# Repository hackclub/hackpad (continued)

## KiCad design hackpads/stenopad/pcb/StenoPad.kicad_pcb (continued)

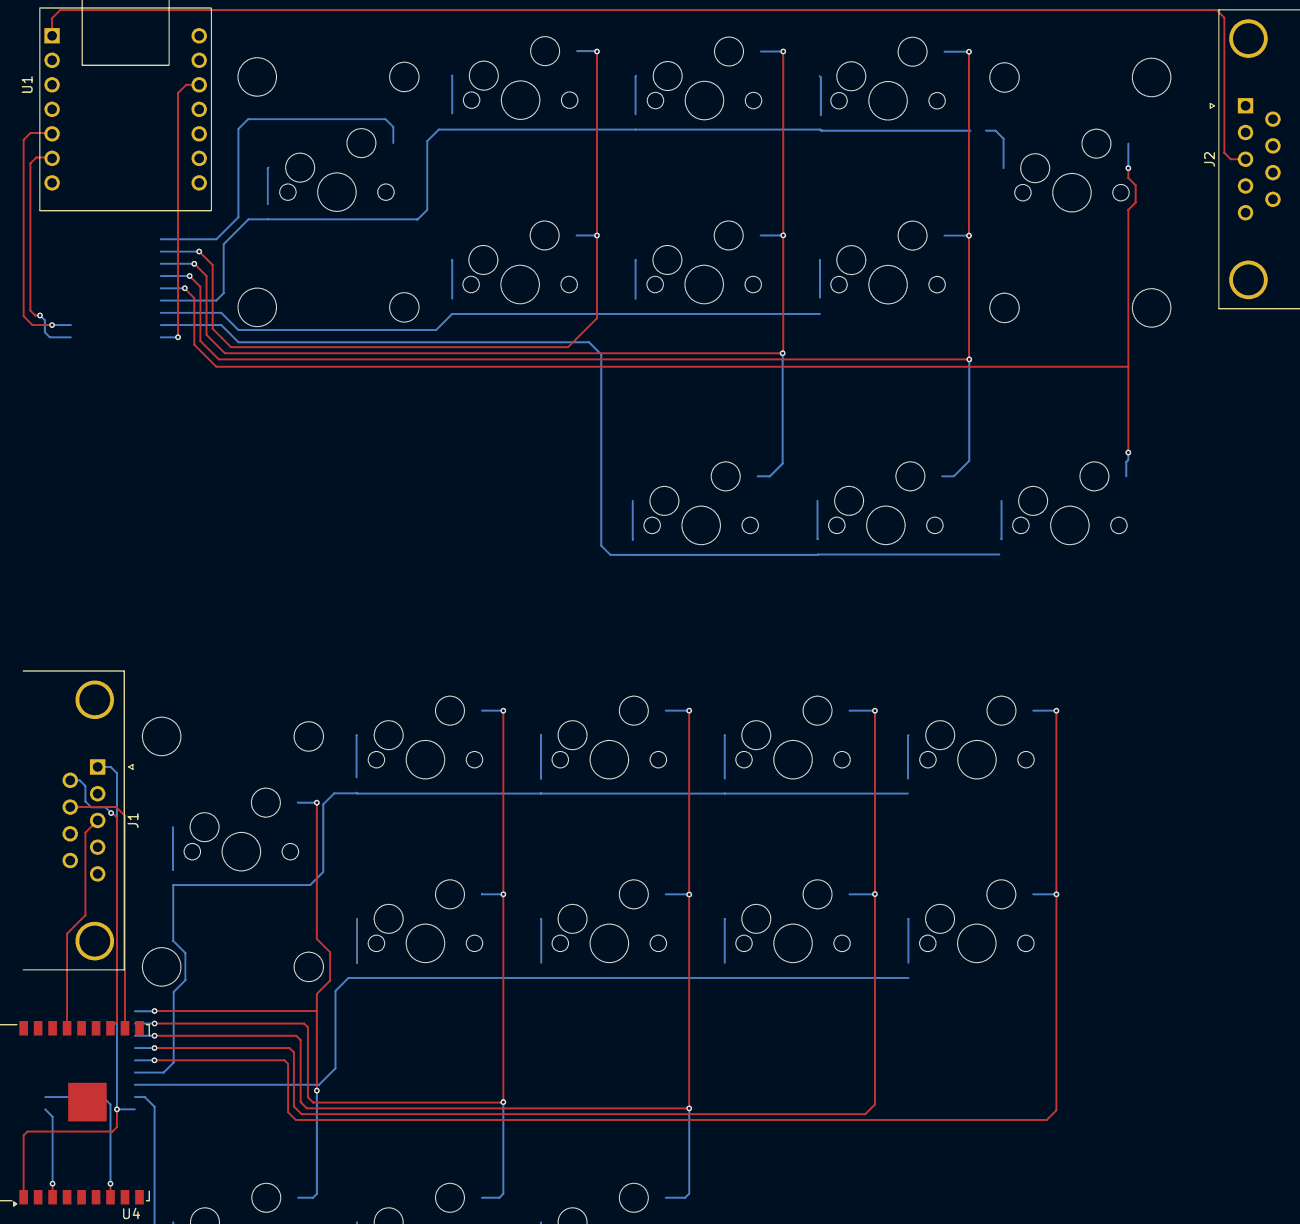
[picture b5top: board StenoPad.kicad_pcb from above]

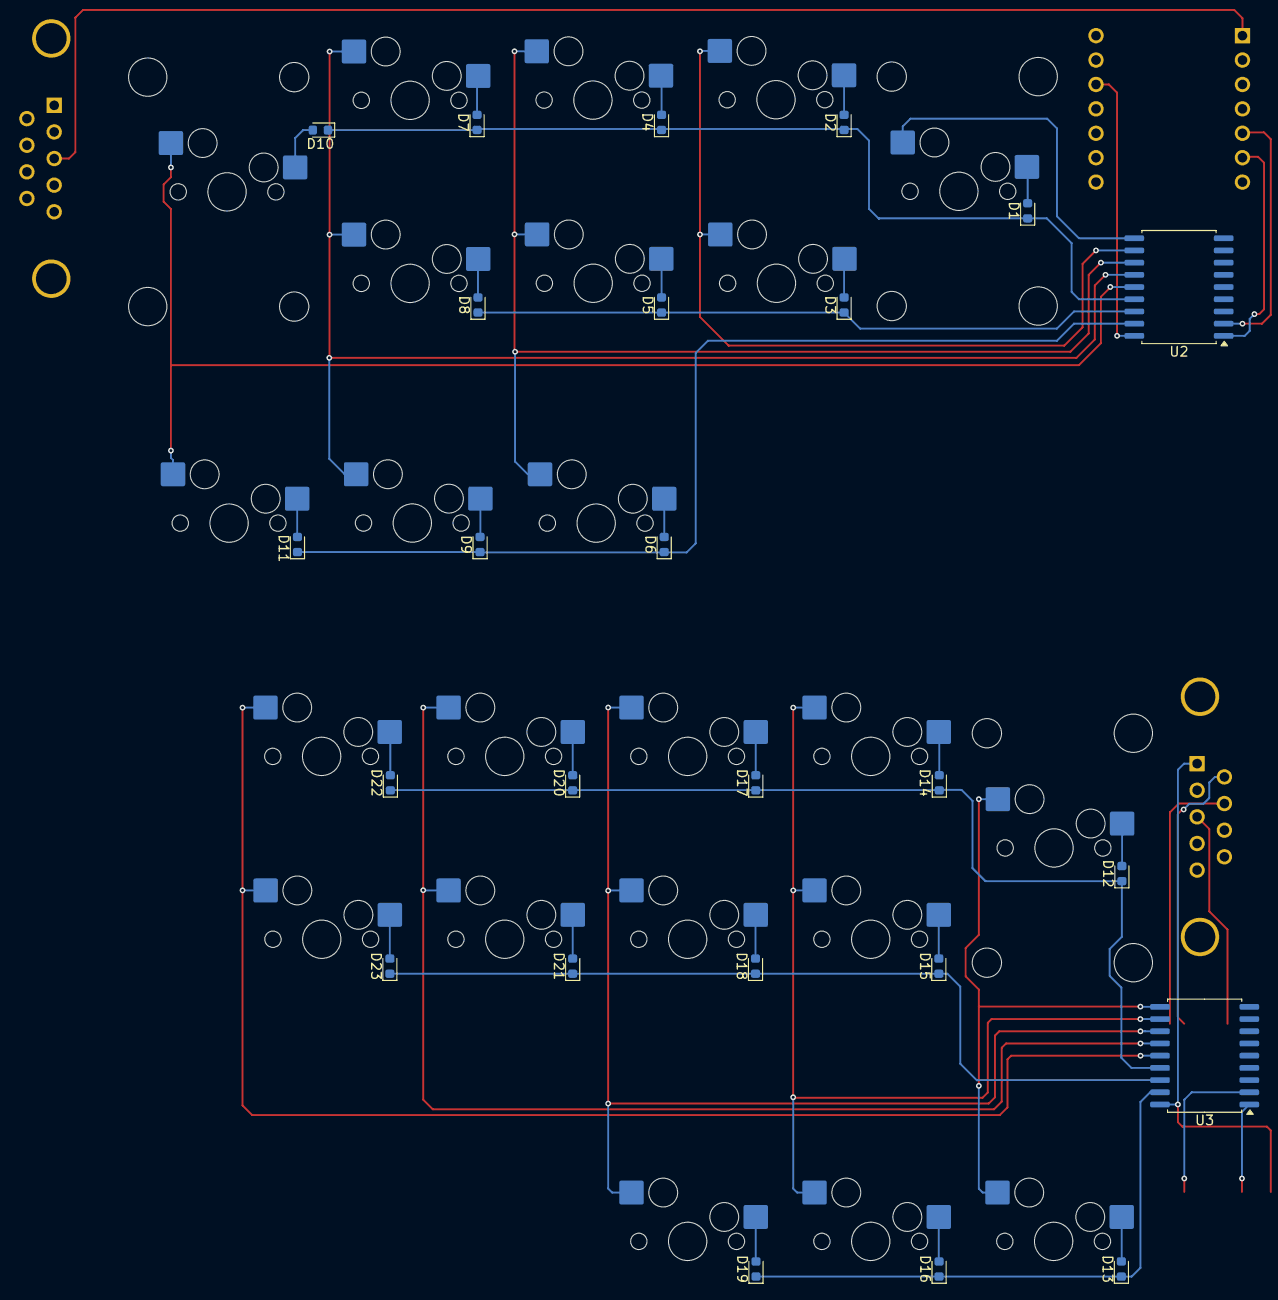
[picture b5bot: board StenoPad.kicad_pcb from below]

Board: 2 copper layers, 52 parts (48 on the bottom side), 54 nets.

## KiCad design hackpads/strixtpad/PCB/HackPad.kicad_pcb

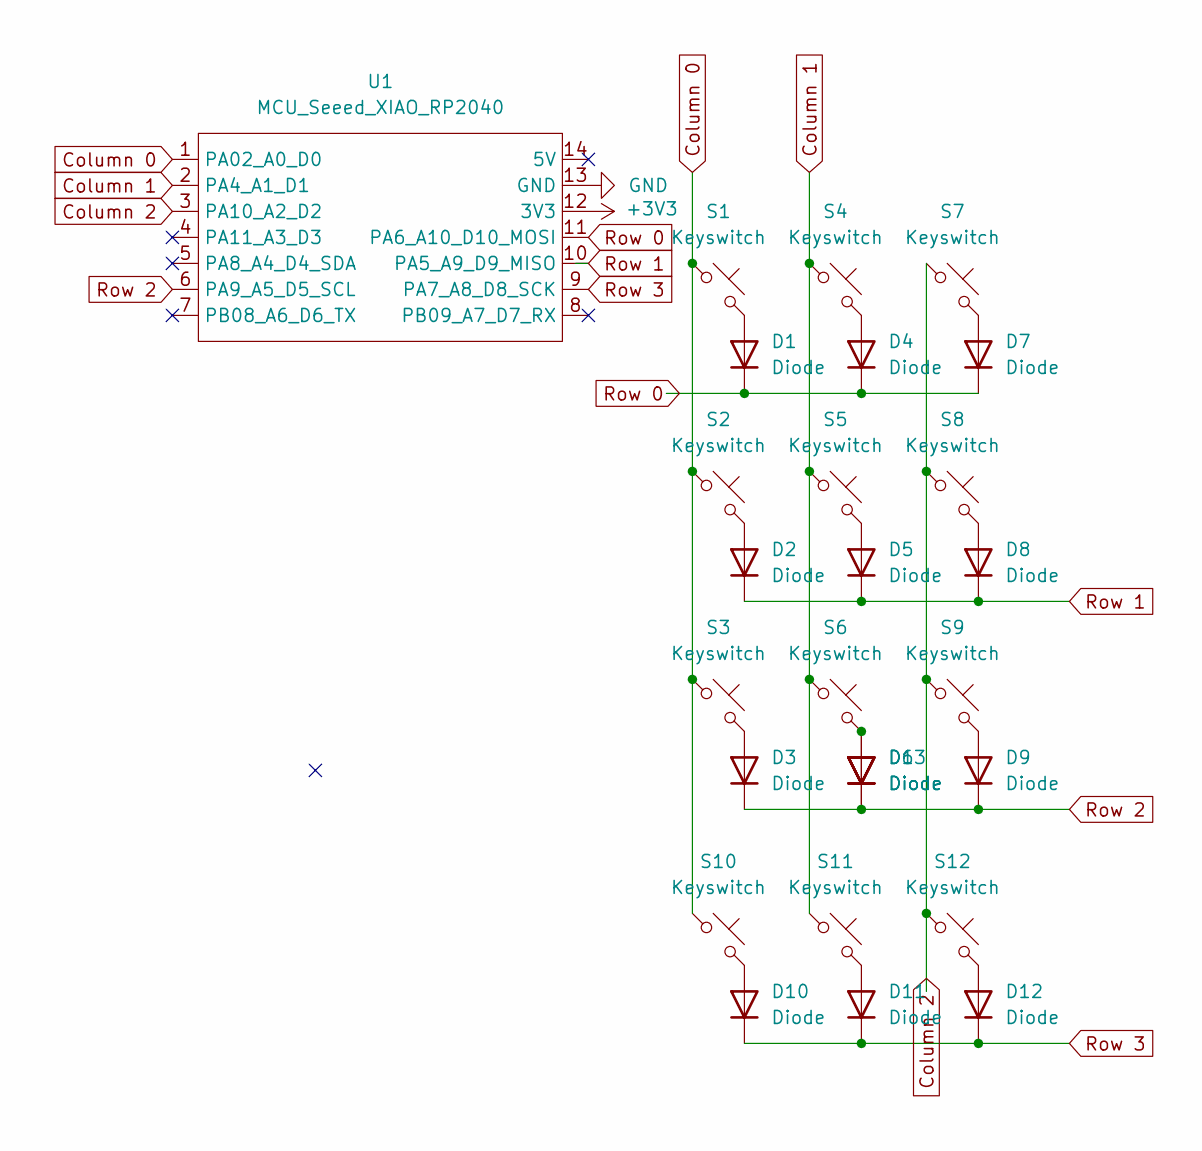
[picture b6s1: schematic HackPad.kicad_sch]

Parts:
D1, D2, D3, D4, D5, D6, D7, D8, D9, D10, D11, D12, D13: Diode; Diode_DO-35
S1, S2, S3, S4, S5, S6, S7, S8, S9, S10, S11, S12: Keyswitch; MX_PCB_1.00u
U1: MCU_Seeed_XIAO_RP2040; Seeed_XIAO_RP2040

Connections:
+3V3: U1.12 (3V3)
Column 0: S1.1, S2.1, S3.1, S10.1, U1.1 (PA02_A0_D0)
Column 1: S4.1, S5.1, S6.1, S11.1, U1.2 (PA4_A1_D1)
Column 2: S7.1, S8.1, S9.1, S12.1, U1.3 (PA10_A2_D2)
GND: U1.13 (GND)
unnamed: D1.2 (A), S1.2
unnamed: D2.2 (A), S2.2
unnamed: D3.2 (A), S3.2
unnamed: D4.2 (A), S4.2
unnamed: D5.2 (A), S5.2
unnamed: D6.2 (A), D13.2 (A), S6.2
unnamed: D7.2 (A), S7.2
unnamed: D8.2 (A), S8.2
unnamed: D9.2 (A), S9.2
unnamed: D10.2 (A), S10.2
unnamed: D11.2 (A), S11.2
unnamed: D12.2 (A), S12.2
Row 0: D1.1 (K), D4.1 (K), D7.1 (K), U1.11 (PA6_A10_D10_MOSI)
Row 1: D2.1 (K), D5.1 (K), D8.1 (K), U1.10 (PA5_A9_D9_MISO)
Row 2: D3.1 (K), D6.1 (K), D9.1 (K), D13.1 (K), U1.6 (PA9_A5_D5_SCL)
Row 3: D10.1 (K), D11.1 (K), D12.1 (K), U1.9 (PA7_A8_D8_SCK)

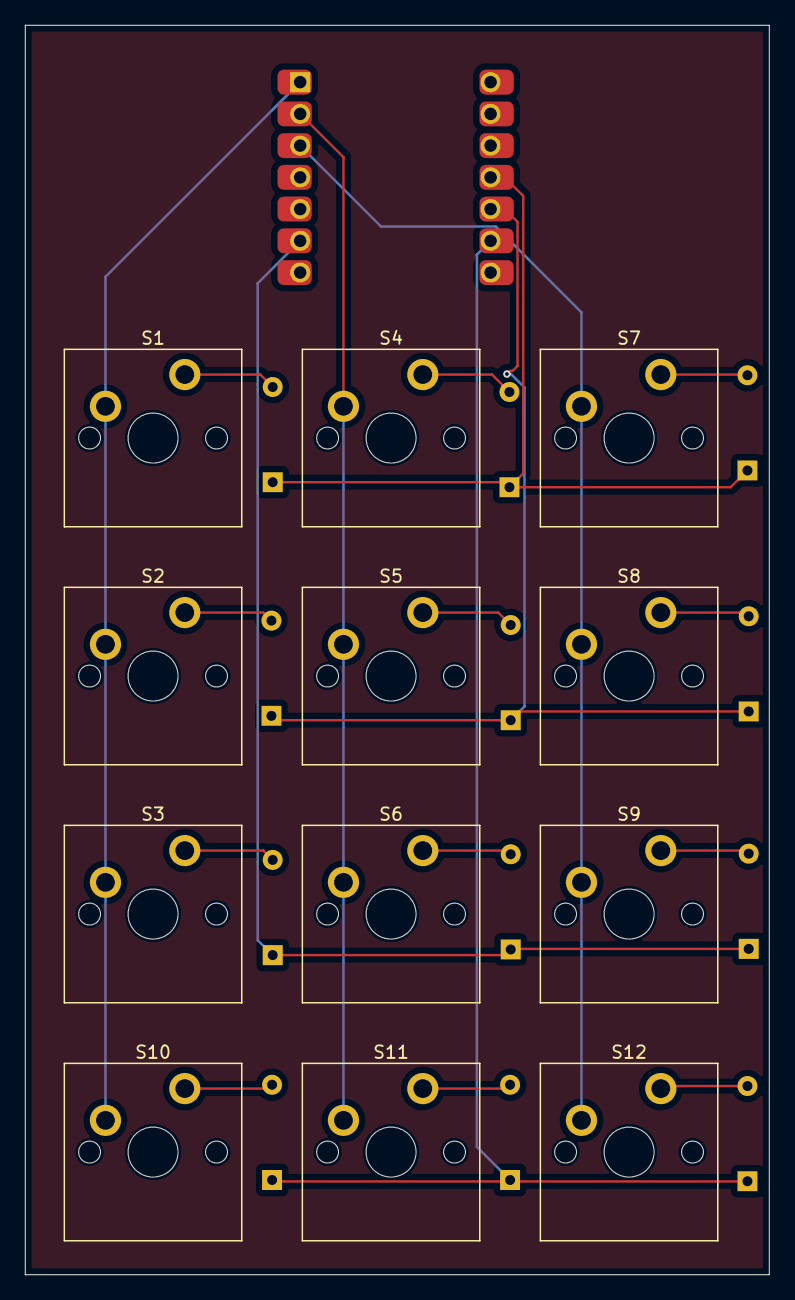
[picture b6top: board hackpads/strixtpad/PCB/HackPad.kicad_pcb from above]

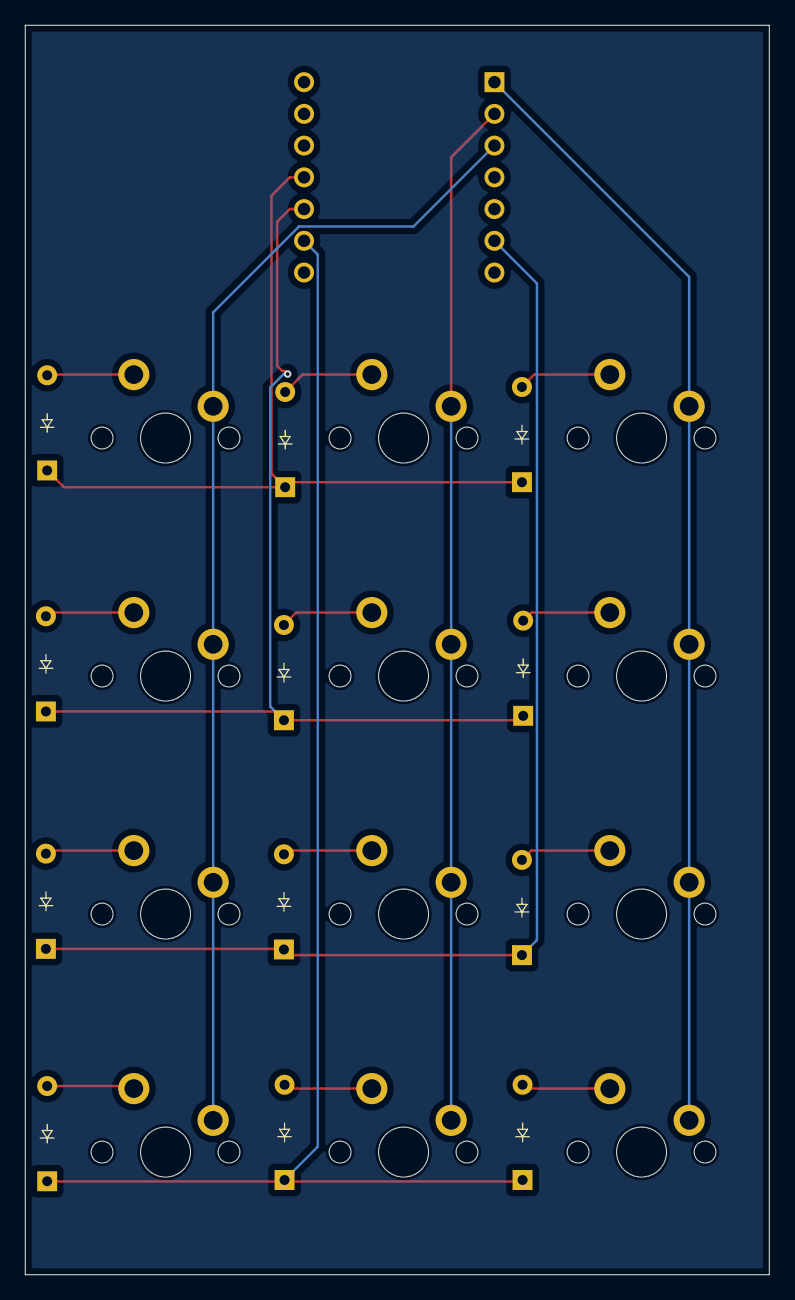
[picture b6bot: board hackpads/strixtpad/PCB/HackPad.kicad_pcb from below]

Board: 2 copper layers, 59.5 x 100.0 mm, 25 parts (12 on the bottom side), 19 nets.

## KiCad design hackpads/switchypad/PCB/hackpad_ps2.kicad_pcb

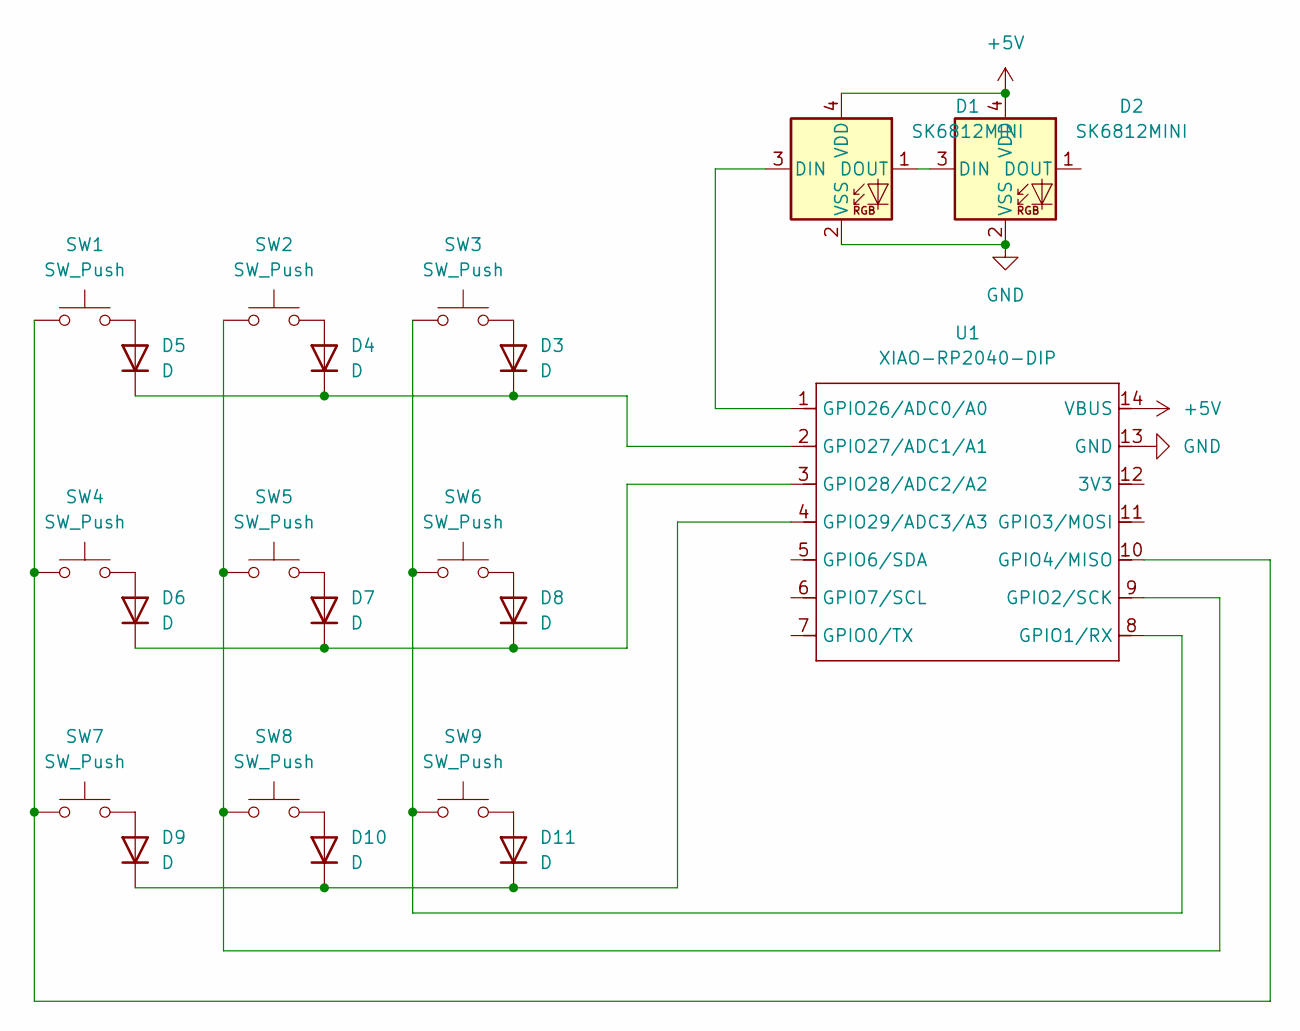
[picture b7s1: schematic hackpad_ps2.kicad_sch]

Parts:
D1, D2: SK6812MINI; LED_SK6812MINI_PLCC4_3.5x3.5mm_P1.75mm
D3, D4, D5, D6, D7, D8, D9, D10, D11: D; D_DO-35_SOD27_P7.62mm_Horizontal
SW1, SW2, SW3, SW4, SW5, SW6, SW7, SW8, SW9: SW_Push; SW_Cherry_MX_1.00u_PCB
U1: XIAO-RP2040-DIP

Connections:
+5V: D1.4 (VDD), D2.4 (VDD), U1.14 (VBUS)
GND: D1.2 (VSS), D2.2 (VSS), U1.13 (GND)
unnamed: D1.3 (DIN), U1.1 (GPIO26/ADC0/A0)
unnamed: D1.1 (DOUT), D2.3 (DIN)
unnamed: D3.2 (A), SW3.2
unnamed: D3.1 (K), D4.1 (K), D5.1 (K), U1.2 (GPIO27/ADC1/A1)
unnamed: D4.2 (A), SW2.2
unnamed: D5.2 (A), SW1.2
unnamed: D6.2 (A), SW4.2
unnamed: D6.1 (K), D7.1 (K), D8.1 (K), U1.3 (GPIO28/ADC2/A2)
unnamed: D7.2 (A), SW5.2
unnamed: D8.2 (A), SW6.2
unnamed: D9.2 (A), SW7.2
unnamed: D10.2 (A), SW8.2
unnamed: D9.1 (K), D10.1 (K), D11.1 (K), U1.4 (GPIO29/ADC3/A3)
unnamed: D11.2 (A), SW9.2
unnamed: SW3.1, SW6.1, SW9.1, U1.8 (GPIO1/RX)
unnamed: SW2.1, SW5.1, SW8.1, U1.9 (GPIO2/SCK)
unnamed: SW1.1, SW4.1, SW7.1, U1.10 (GPIO4/MISO)

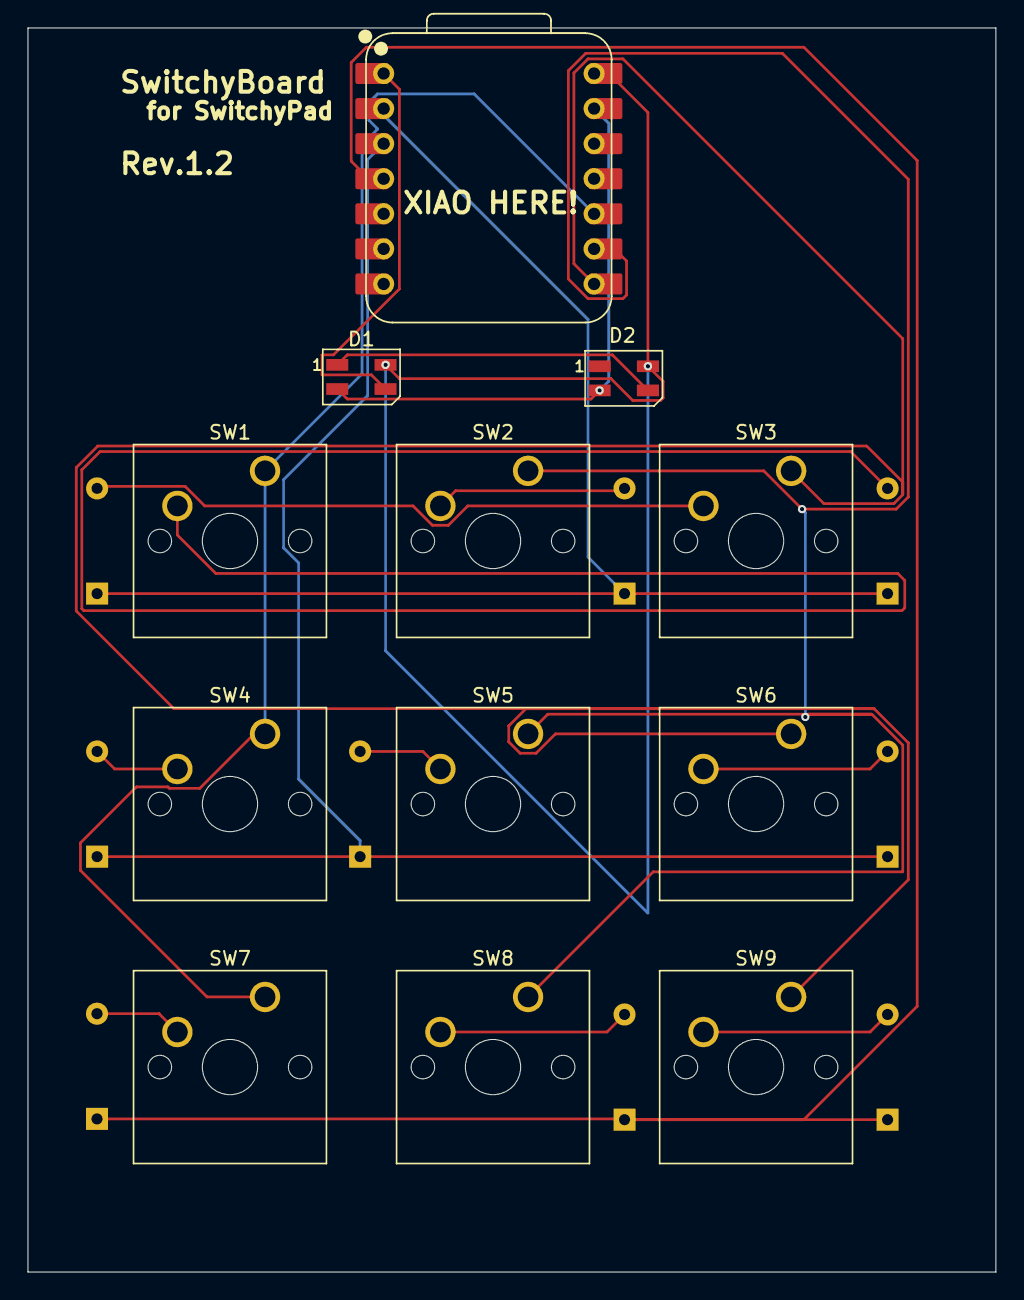
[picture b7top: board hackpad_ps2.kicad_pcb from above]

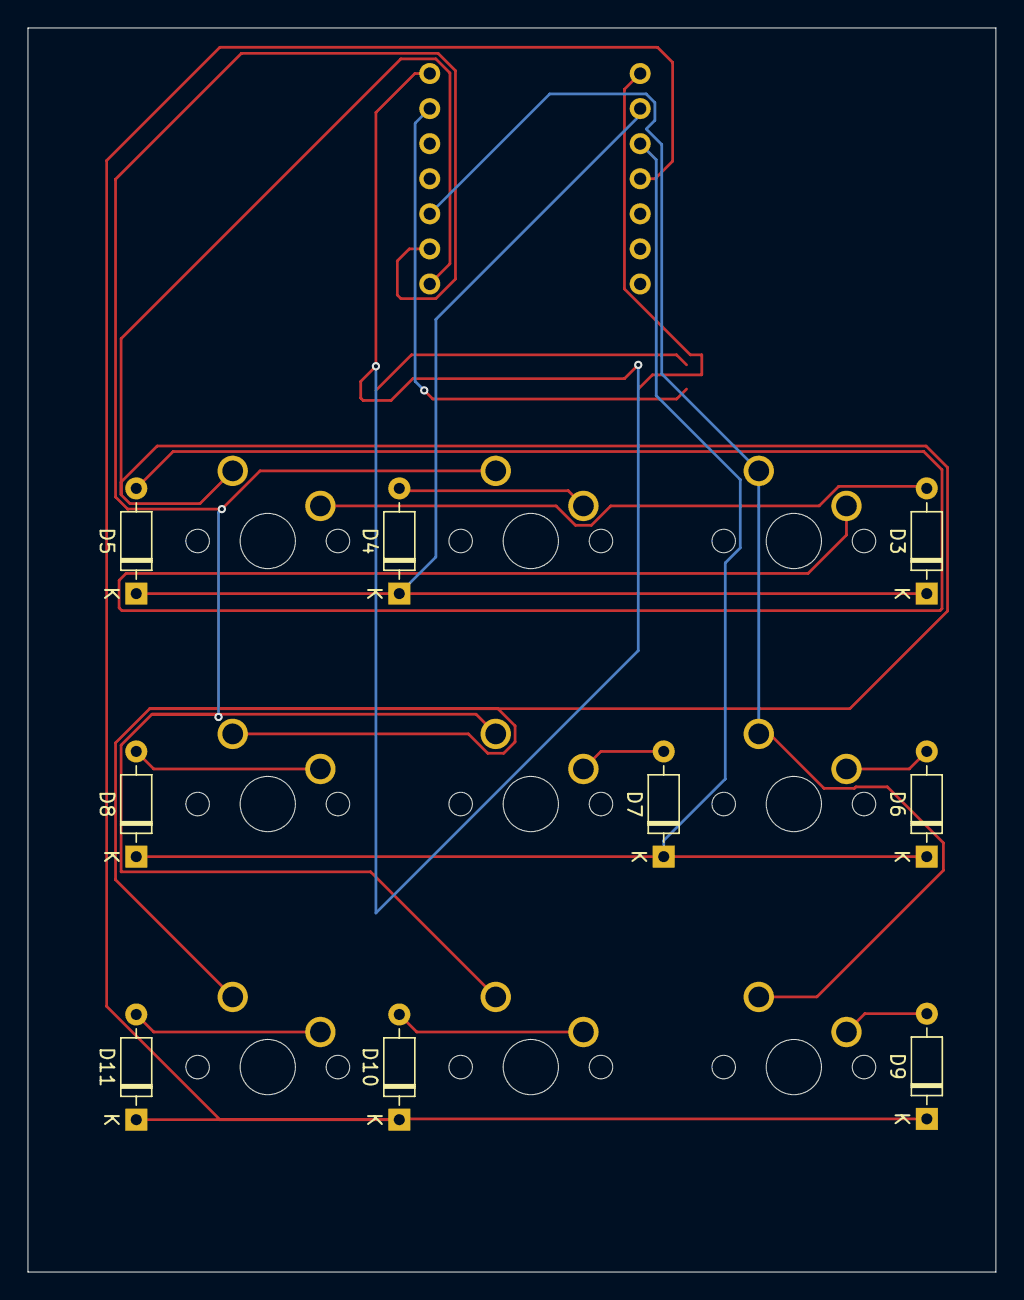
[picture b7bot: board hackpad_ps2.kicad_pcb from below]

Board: 2 copper layers, 70.1 x 90.1 mm, 21 parts (9 on the bottom side), 19 nets.

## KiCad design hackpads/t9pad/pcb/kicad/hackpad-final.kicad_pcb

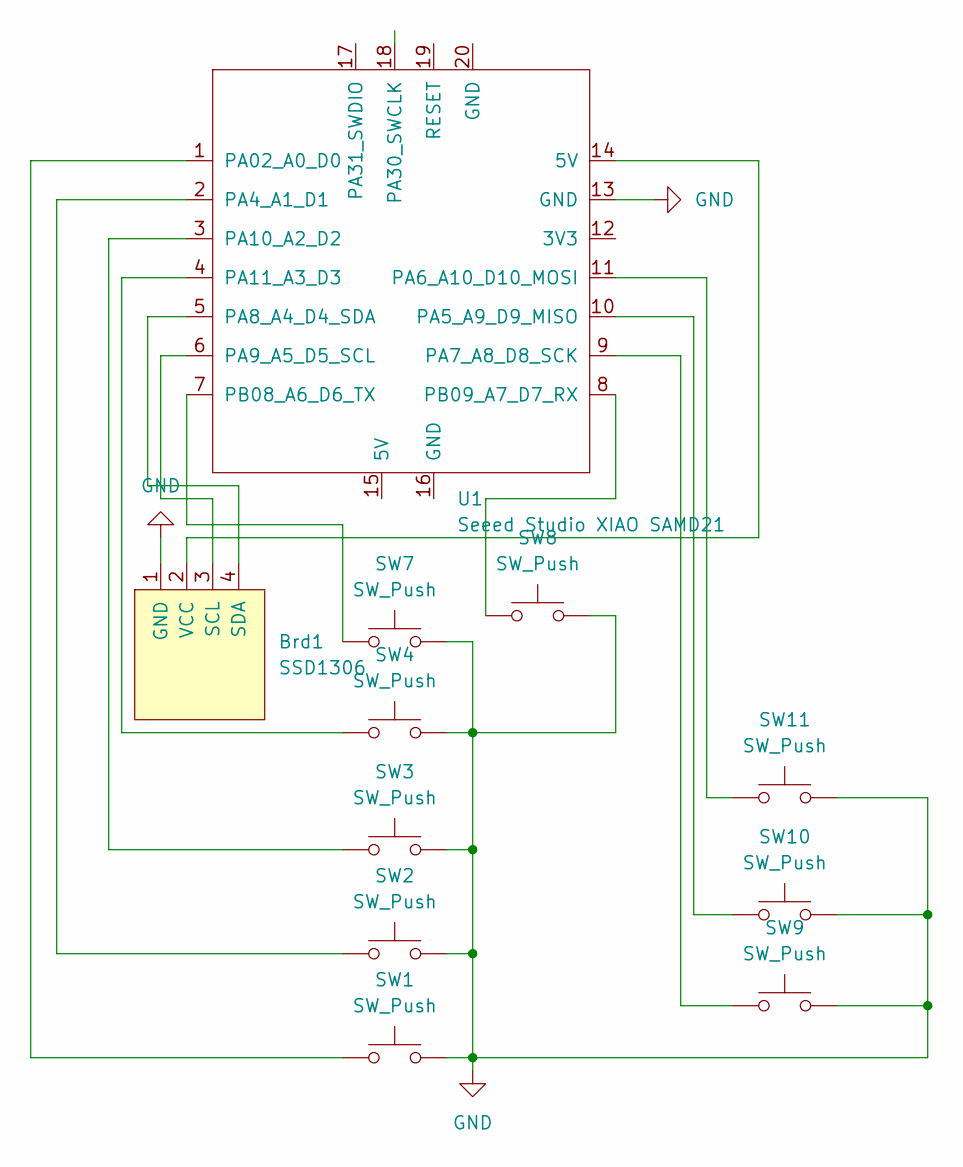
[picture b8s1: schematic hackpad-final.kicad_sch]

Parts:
Brd1: SSD1306; 128x64OLED
SW1, SW2, SW3, SW4, SW7, SW8, SW9, SW10, SW11: SW_Push; SW_Cherry_MX_1.00u_PCB
U1: Seeed Studio XIAO SAMD21; XIAO-Generic-Thruhole-14P-2.54-21X17.8MM

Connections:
GND: Brd1.1 (GND), SW1.2, SW2.2, SW3.2, SW4.2, SW7.2, SW8.2, SW9.2, SW10.2, SW11.2, U1.13 (GND)
unnamed: Brd1.3 (SCL), U1.6 (PA9_A5_D5_SCL)
unnamed: Brd1.4 (SDA), U1.5 (PA8_A4_D4_SDA)
unnamed: Brd1.2 (VCC), U1.14 (5V)
unnamed: SW1.1, U1.1 (PA02_A0_D0)
unnamed: SW2.1, U1.2 (PA4_A1_D1)
unnamed: SW10.1, U1.10 (PA5_A9_D9_MISO)
unnamed: SW11.1, U1.11 (PA6_A10_D10_MOSI)
unnamed: SW9.1, U1.9 (PA7_A8_D8_SCK)
unnamed: SW3.1, U1.3 (PA10_A2_D2)
unnamed: SW4.1, U1.4 (PA11_A3_D3)
unnamed: SW7.1, U1.7 (PB08_A6_D6_TX)
unnamed: SW8.1, U1.8 (PB09_A7_D7_RX)

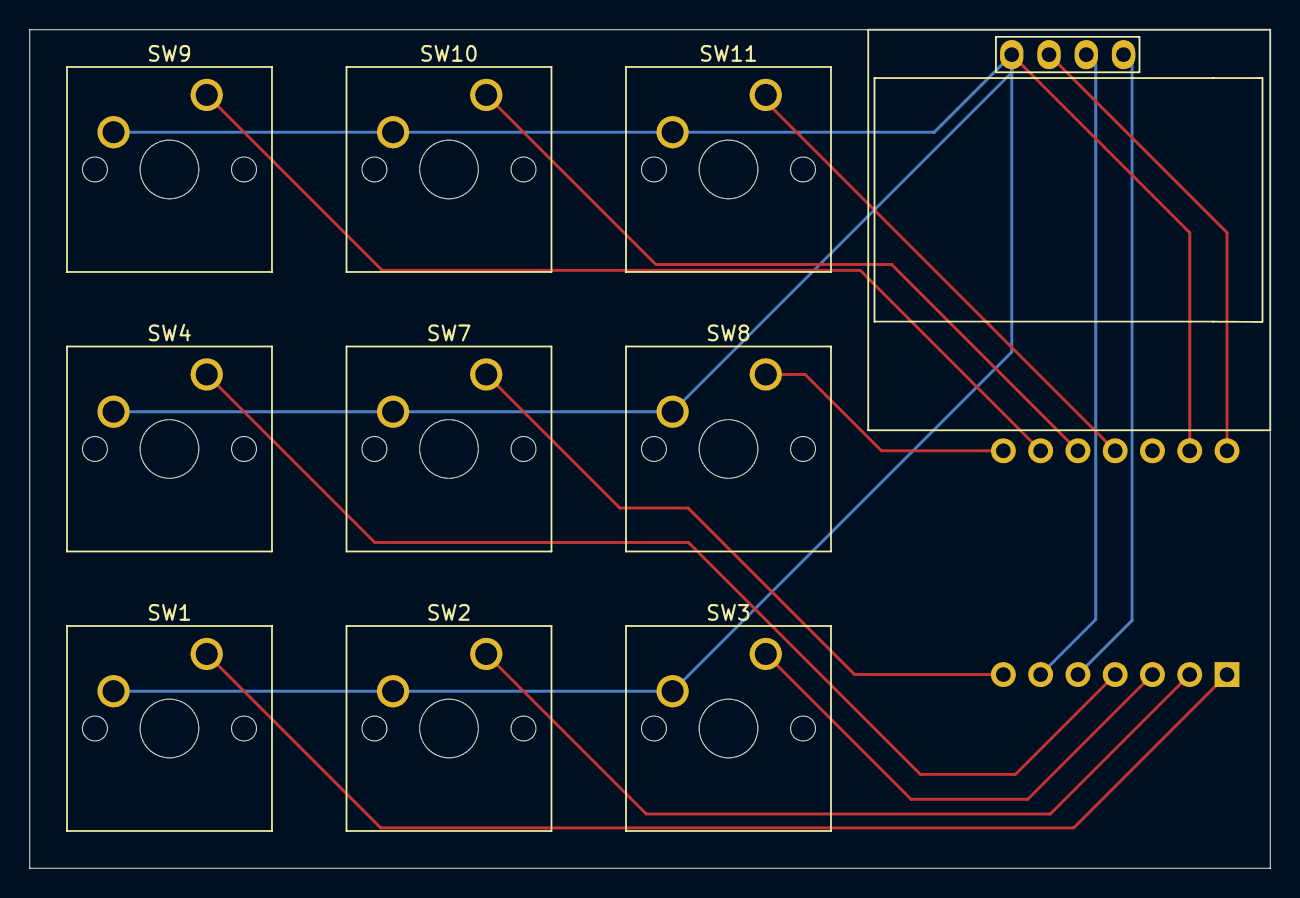
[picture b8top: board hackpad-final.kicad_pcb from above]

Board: 2 copper layers, 84.5 x 57.2 mm, 11 parts (1 on the bottom side), 13 nets.
